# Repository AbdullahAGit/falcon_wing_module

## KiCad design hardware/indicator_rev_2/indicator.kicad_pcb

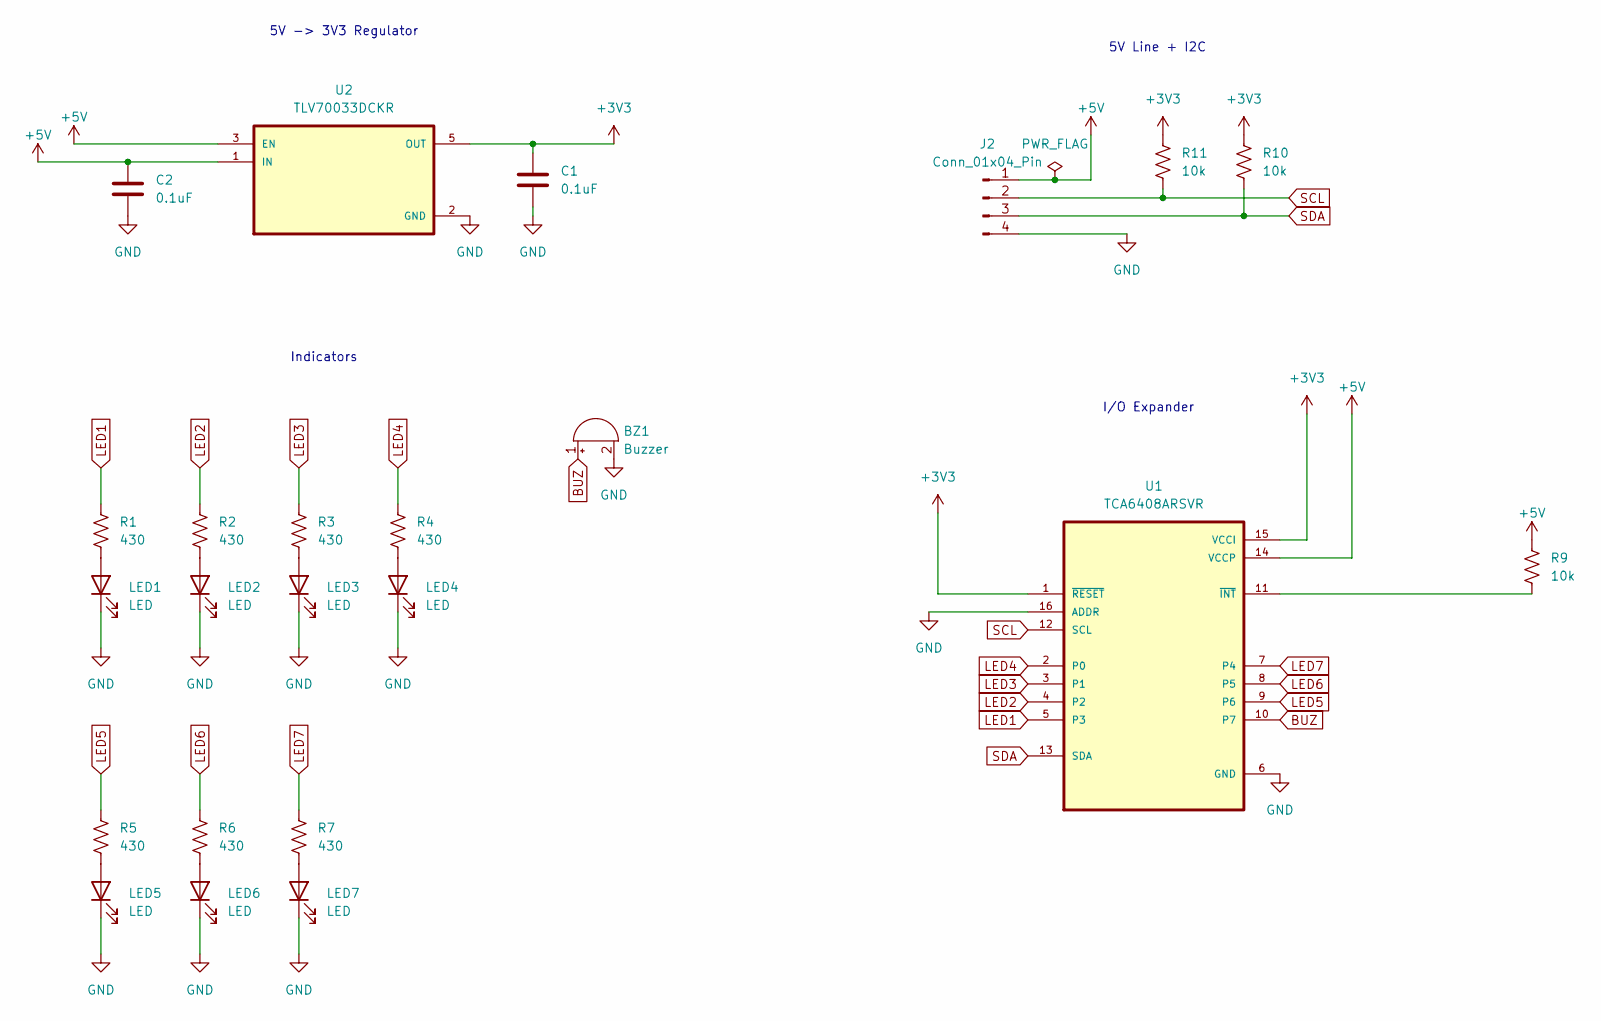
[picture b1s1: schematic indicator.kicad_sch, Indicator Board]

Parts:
BZ1: Buzzer; Buzzer_12x9.5RM7.6
C1, C2: 0.1uF; C_0603_1608Metric
J2: Conn_01x04_Pin; JST_XH_B4B-XH-A_1x04_P2.50mm_Vertical
LED1, LED2, LED3, LED4, LED5, LED6, LED7: LED; LED_D4.0mm
R1, R2, R3, R4, R5, R6, R7: 430; R_0603_1608Metric
R9, R10, R11: 10k; R_0603_1608Metric
U1: TCA6408ARSVR; QFN40P180X260X55-16N
U2: TLV70033DCKR; SOT65P210X110-5N

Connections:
+3V3: C1.1, R10.2, R11.2, U1.1 (~RESET), U1.15 (VCCI), U2.5 (OUT)
+5V: C2.1, J2.1, R9.2, U1.14 (VCCP), U2.1 (IN), U2.3 (EN)
BUZ: BZ1.1 (-), U1.10 (P7)
GND: BZ1.2 (+), C1.2, C2.2, J2.4, LED1.1 (K), LED2.1 (K), LED3.1 (K), LED4.1 (K), LED5.1 (K), LED6.1 (K), LED7.1 (K), U1.6 (GND), U1.16 (ADDR), U2.2 (GND)
LED1: R1.2, U1.5 (P3)
LED2: R2.2, U1.4 (P2)
LED3: R3.2, U1.3 (P1)
LED4: R4.2, U1.2 (P0)
LED5: R5.2, U1.9 (P6)
LED6: R6.2, U1.8 (P5)
LED7: R7.2, U1.7 (P4)
unnamed: LED1.2 (A), R1.1
unnamed: LED2.2 (A), R2.1
unnamed: LED3.2 (A), R3.1
unnamed: LED4.2 (A), R4.1
unnamed: LED5.2 (A), R5.1
unnamed: LED6.2 (A), R6.1
unnamed: LED7.2 (A), R7.1
unnamed: R9.1, U1.11 (~INT)
SCL: J2.2, R11.1, U1.12 (SCL)
SDA: J2.3, R10.1, U1.13 (SDA)

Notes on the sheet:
5V Line + I2C
I/O Expander
5V -> 3V3 Regulator
Indicators

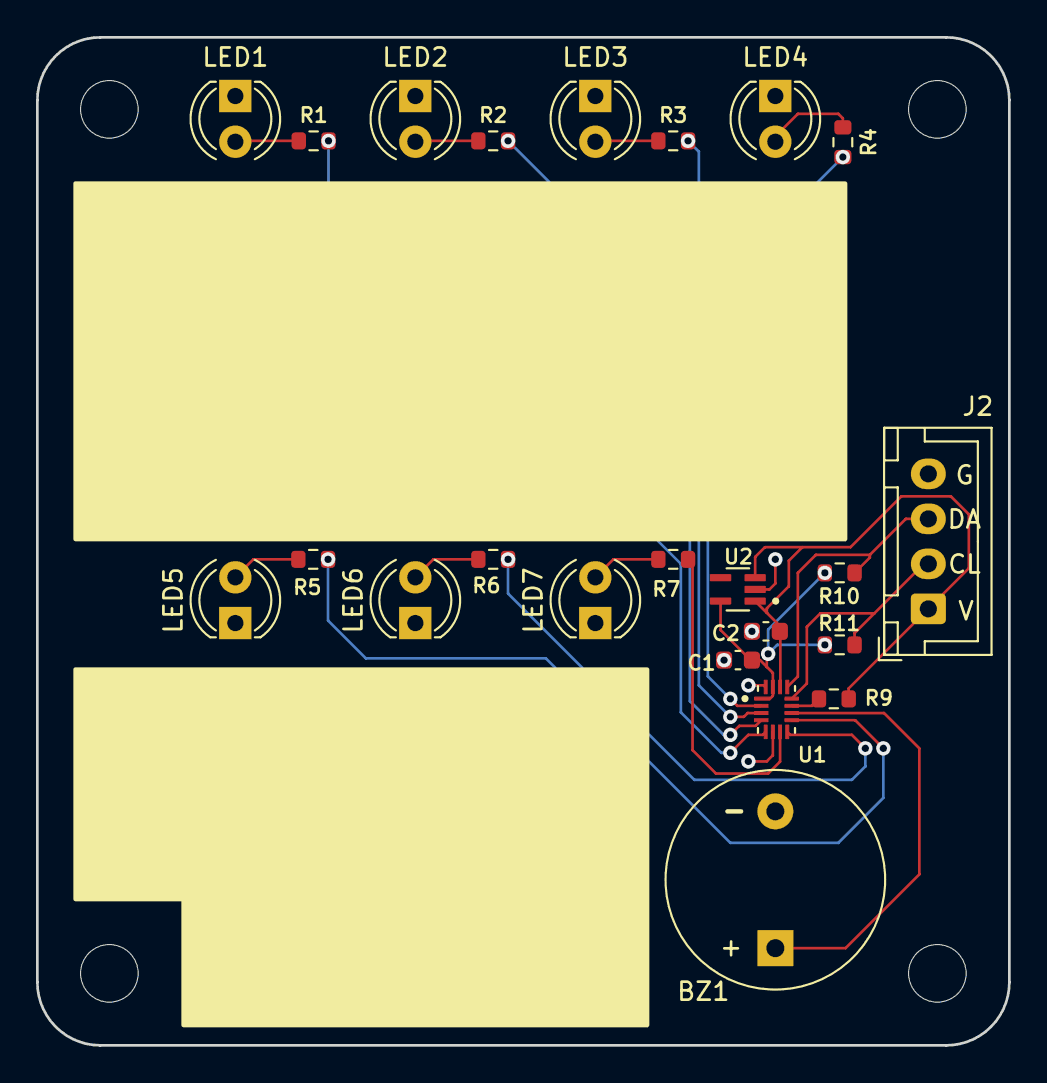
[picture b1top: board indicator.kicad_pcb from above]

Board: 2 copper layers, 54.0 x 56.0 mm, 23 parts (0 on the bottom side), 21 nets.

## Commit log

2025-09-01 updated board, added symbol files
